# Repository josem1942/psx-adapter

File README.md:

# psx-adapter

This is both a hardware and software project that allows you to connect a DualShock 1 or DualShock 2 (untested) controller to a PC. This works by reading the signals from the controller and converting them to USB HID commands, so in theory it should support any device that supports USB HID GamePads.

## Hardware

The main microcontroller used is the RP2040. The board is designed with heavy inspiration from the Raspberry Pi Pico, as such many of the parts are similar if not identical to the Pico. As for the the header, you can typically find some on AliExpress to order. The whole project is designed using KiCad, so as long as you have that installed, you should be able to open it.

## Firmware

The firmware is built with the pico-sdk and TinyUSB.

### Building and Flashing

This was built on macOS, but I'm pretty sure you can build it on Windows and Linux if you get the same dependencies.

Dependencies:
- CMake 3.13 or newer
- Make
- [Arm GNU Toolchain](https://developer.arm.com/downloads/-/arm-gnu-toolchain-downloads)
- Python 3
- Git
- GCC/G++ or whatever compiler you use to build C/C++ 

Install the required dependencies using `brew`:

```
brew install --cask gcc-arm-embedded
brew install cmake ninja python git picotool
```

Clone the repository:

```
git clone --recurse-submodules=firmware/pico-sdk https://github.com/josem1942/psx-adapter.git
cd psx-adapter
git -C firmware/pico-sdk submodule update --init lib/tinyusb
```

Then finally, you can build the firmware:

```
mkdir firmware/build
cd firmware/build
cmake ..
make
```

Then, to flash, hold down `SW1` (the only button) on the board while plugging in the USB, then drag `firmware/build/psxc.uf2` to the drive that appears when you plugged in the board.

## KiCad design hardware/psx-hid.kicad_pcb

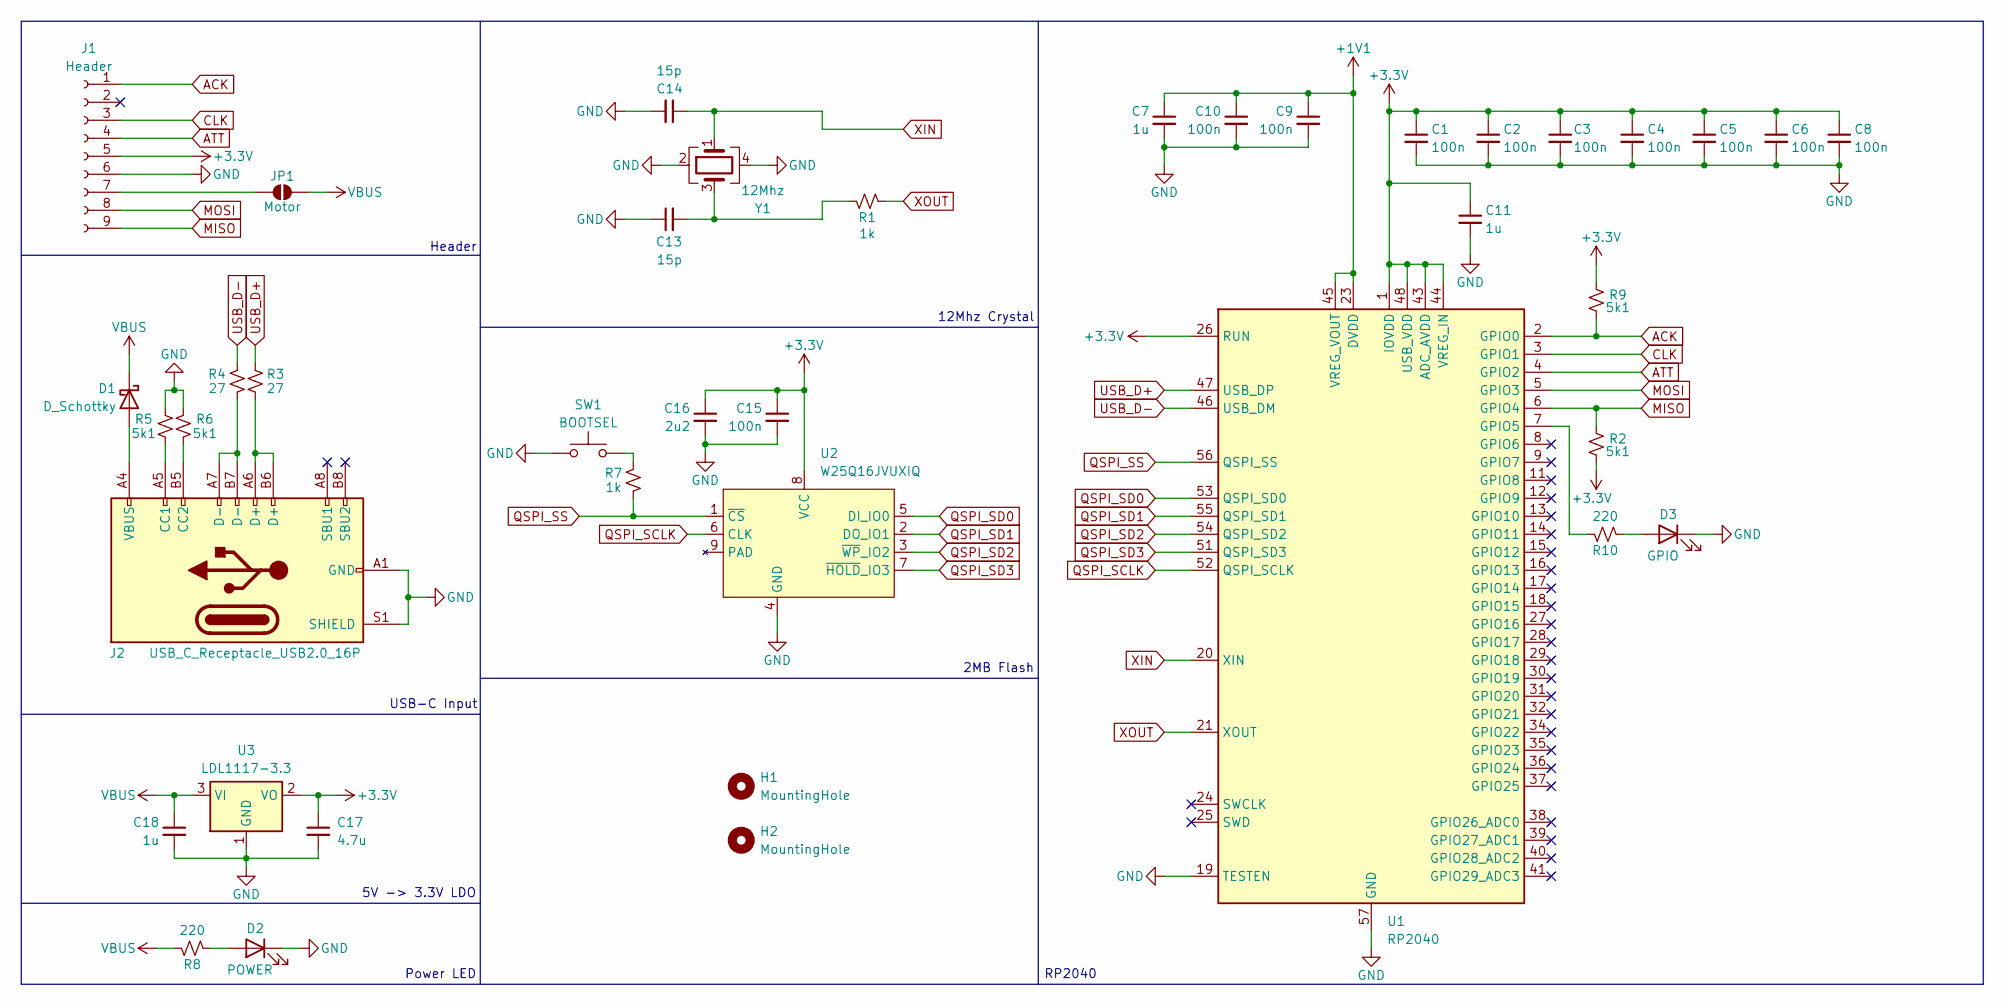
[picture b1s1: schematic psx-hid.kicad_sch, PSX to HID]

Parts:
C1, C2, C3, C4, C5, C6, C8, C9, C10, C15: 100n; C_0603_1608Metric; Mfr. # CC0603KRX7R9BB104; LCSC C14663
C7, C11, C18: 1u; C_0603_1608Metric; Mfr. # CL10A105KB8NNNC; LCSC C15849
C13, C14: 15p; C_0603_1608Metric; Mfr. # CL10C150JB8NNNC; LCSC C1644
C16: 2u2; C_0805_2012Metric; Mfr. # CL21A225KBQNNNE; LCSC C377773
C17: 4.7u; C_0603_1608Metric; Mfr. # CL10A475KO8NNNC; LCSC C19666
D1: D_Schottky; D_SOD-123F; Mfr. # B5819W SL; LCSC C8598
D2: POWER; LED_0805_2012Metric; Mfr. # NCD0805R1; LCSC C84256
D3: GPIO; LED_0805_2012Metric; Mfr. # NCD0805R1; LCSC C84256
H1, H2: MountingHole; MountingHole_3.2mm_M3
J1: Header; PSX_Interface
J2: USB_C_Receptacle_USB2.0_16P; USB_C_Receptacle_GCT_USB4105-xx-A_16P_TopMnt_Horizontal; Mfr. # USB4105-GF-A-060; LCSC C3025063
JP1: Motor; SolderJumper-2_P1.3mm_Open_Pad1.0x1.5mm
R1, R7: 1k; R_0603_1608Metric; Mfr. # 0603WAF1001T5E; LCSC C21190
R2, R5, R6, R9: 5k1; R_0402_1005Metric; Mfr. # 0402WGF5101TCE; LCSC C25905
R3, R4: 27; R_0402_1005Metric; Mfr. # 0402WGF270JTCE; LCSC C25100
R8, R10: 220; R_0402_1005Metric; Mfr. # 0402WGF2200TCE; LCSC C25091
SW1: BOOTSEL; SW_Push_1P1T_NO_CK_KMR2; Mfr. # KMR211GLFS; LCSC C221675
U1: RP2040; QFN-56-1EP_7x7mm_P0.4mm_EP3.2x3.2mm; Mfr. # RP2040; LCSC C2040
U2: W25Q16JVUXIQ; Winbond_USON-8-1EP_3x2mm_P0.5mm_EP0.2x1.6mm; Mfr. # GD25Q16EEIGR; LCSC C2986331
U3: LDL1117-3.3; SOT-223-3_TabPin2; Mfr. # LDL1117S33R; LCSC C435835
Y1: 12Mhz; Crystal_SMD_Abracon_ABM8G-4Pin_3.2x2.5mm; Mfr. # ABM8-272-T3; LCSC C20625731

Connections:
+1V1: C7.1, C9.1, C10.1, U1.23 (DVDD), U1.45 (VREG_VOUT), U1.50 (DVDD)
+3.3V: C1.1, C2.1, C3.1, C4.1, C5.1, C6.1, C8.1, C11.1, C15.1, C16.1, C17.1, J1.5, R2.2, R9.1, U1.1 (IOVDD), U1.10 (IOVDD), U1.22 (IOVDD), U1.26 (RUN), U1.33 (IOVDD), U1.42 (IOVDD), U1.43 (ADC_AVDD), U1.44 (VREG_IN), U1.48 (USB_VDD), U1.49 (IOVDD), U2.8 (VCC), U3.2 (VO)
ACK: J1.1, R9.2, U1.2 (GPIO0)
ATT: J1.4, U1.4 (GPIO2)
CLK: J1.3, U1.3 (GPIO1)
GND: C1.2, C2.2, C3.2, C4.2, C5.2, C6.2, C7.2, C8.2, C9.2, C10.2, C11.2, C13.1, C14.2, C15.2, C16.2, C17.2, C18.2, D2.1 (K), D3.1 (K), J1.6, J2.A1 (GND), J2.A12 (GND), J2.B1 (GND), J2.B12 (GND), J2.S1 (SHIELD), R5.2, R6.2, SW1.1, U1.19 (TESTEN), U1.57 (GND), U2.4 (GND), U3.1 (GND), Y1.2, Y1.4
MISO: J1.9, R2.1, U1.6 (GPIO4)
MOSI: J1.8, U1.5 (GPIO3)
unnamed: C13.2, R1.1, Y1.3
unnamed: D1.2 (A), J2.A4 (VBUS), J2.A9 (VBUS), J2.B4 (VBUS), J2.B9 (VBUS)
unnamed: D2.2 (A), R8.2
unnamed: D3.2 (A), R10.2
unnamed: J1.7, JP1.1 (A)
unnamed: J2.A5 (CC1), R5.1
unnamed: J2.B5 (CC2), R6.1
unnamed: J2.A6 (D+), J2.B6 (D+), R3.2
unnamed: J2.A7 (D-), J2.B7 (D-), R4.2
unnamed: R7.1, SW1.2
unnamed: R10.1, U1.7 (GPIO5)
QSPI_SCLK: U1.52 (QSPI_SCLK), U2.6 (CLK)
QSPI_SD0: U1.53 (QSPI_SD0), U2.5 (DI_IO0)
QSPI_SD1: U1.55 (QSPI_SD1), U2.2 (DO_IO1)
QSPI_SD2: U1.54 (QSPI_SD2), U2.3 (~WP_IO2)
QSPI_SD3: U1.51 (QSPI_SD3), U2.7 (~HOLD_IO3)
QSPI_SS: R7.2, U1.56 (QSPI_SS), U2.1 (~CS)
USB_D+: R3.1, U1.47 (USB_DP)
USB_D-: R4.1, U1.46 (USB_DM)
VBUS: C18.1, D1.1 (K), JP1.2 (B), R8.1, U3.3 (VI)
XIN: C14.1, U1.20 (XIN), Y1.1
XOUT: R1.2, U1.21 (XOUT)

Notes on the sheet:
Header
5V -> 3.3V LDO
2MB Flash
12Mhz Crystal
USB-C Input
Power LED
RP2040

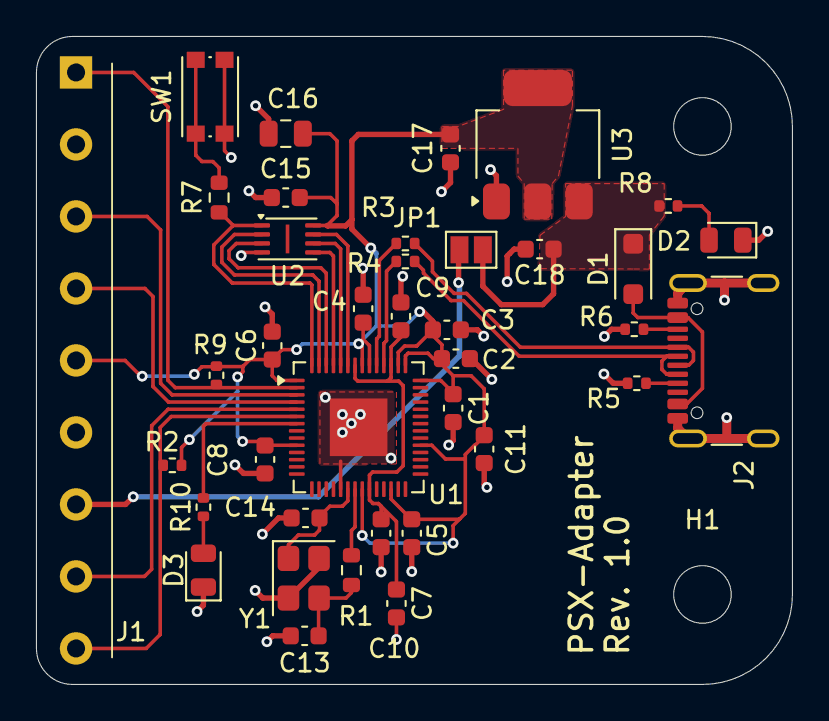
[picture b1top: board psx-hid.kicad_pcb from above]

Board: 2 copper layers, 42.0 x 36.0 mm, 40 parts (0 on the bottom side), 30 nets.
